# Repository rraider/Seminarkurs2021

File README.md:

# Seminarkurs2021

  Entwicklung eines turingvollständigen, primitiven Microcontroller in der Software Digital
  
  Sponsored by JLCPCB https://jlcpcb.com/RAT

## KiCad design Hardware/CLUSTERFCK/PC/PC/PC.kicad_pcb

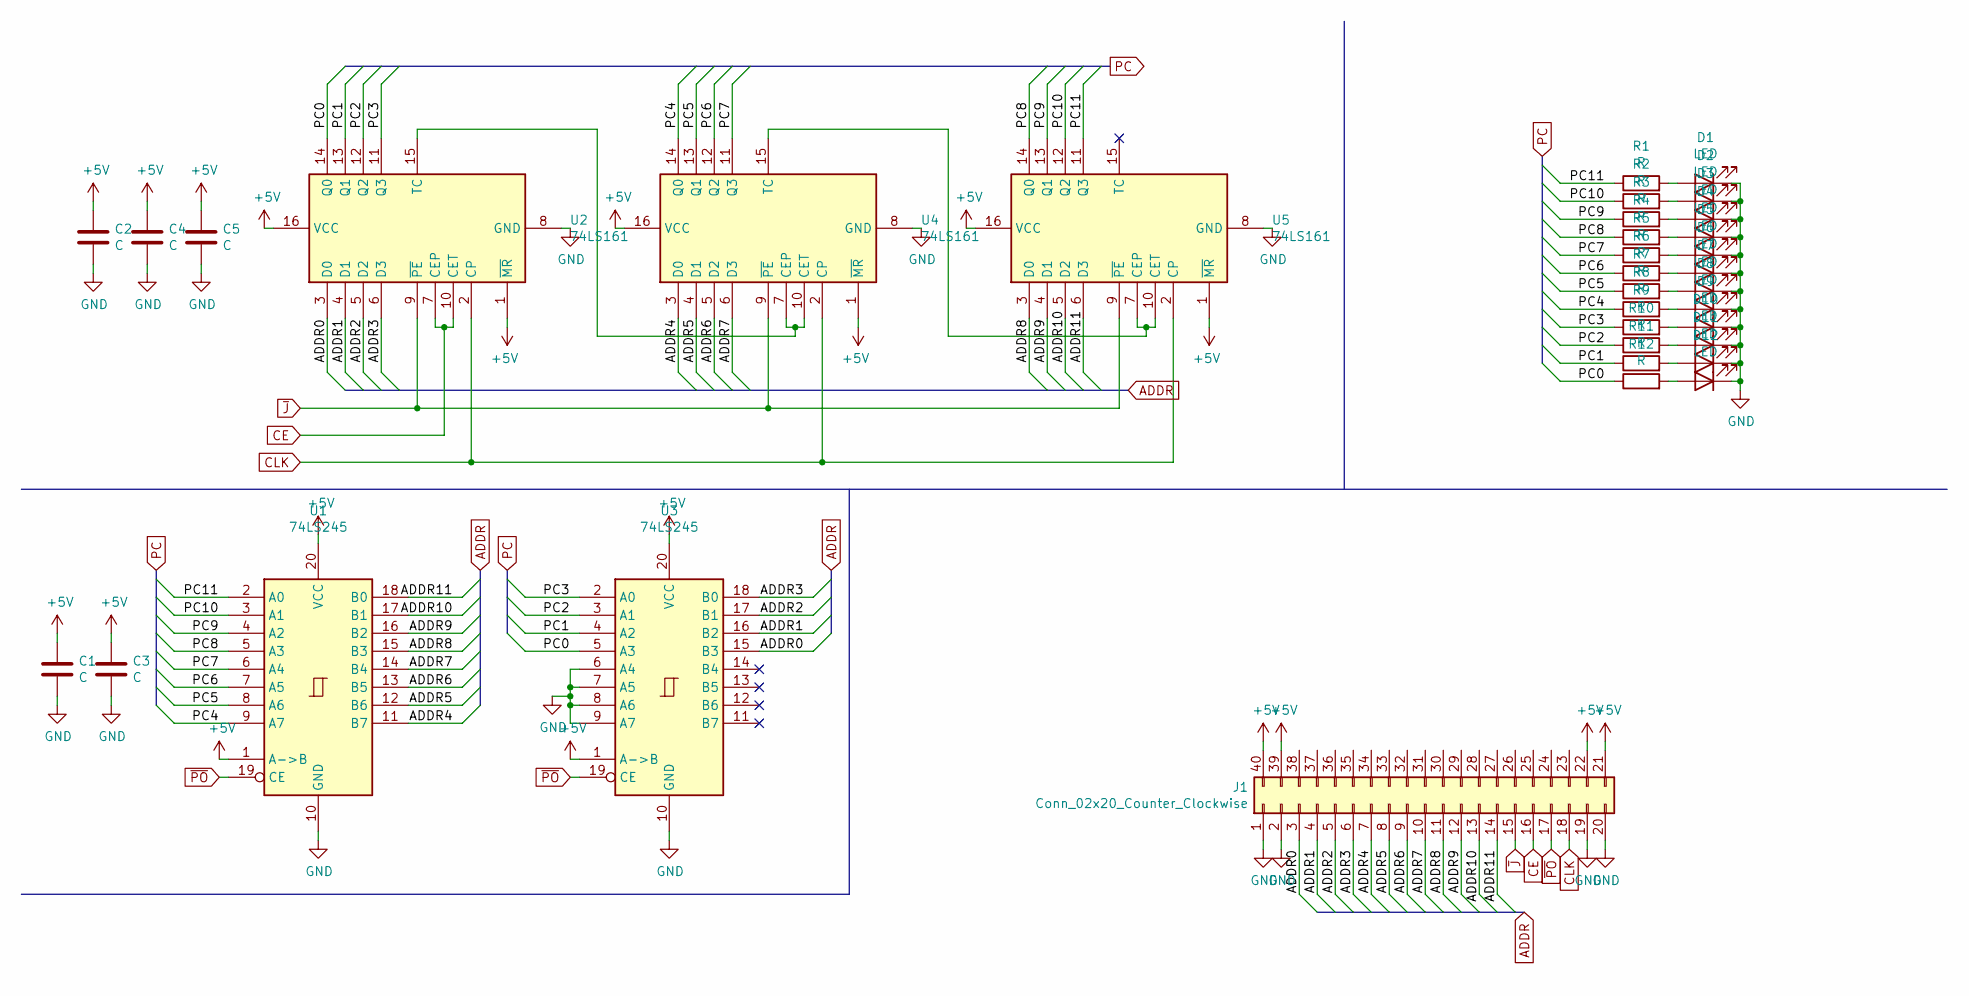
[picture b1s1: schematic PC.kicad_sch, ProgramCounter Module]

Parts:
C1, C2, C3, C4, C5: C; C_0805_2012Metric_Pad1.15x1.40mm_HandSolder
D1, D2, D3, D4, D5, D6, D7, D8, D9, D10, D11, D12: LED; LED_D5.0mm
J1: Conn_02x20_Counter_Clockwise; PinSocket_2x20_P2.54mm_Horizontal
R1, R2, R3, R4, R5, R6, R7, R8, R9, R10, R11, R12: R; R_0805_2012Metric_Pad1.15x1.40mm_HandSolder
U1, U3: 74LS245; SOIC-20W_7.5x12.8mm_P1.27mm
U2, U4, U5: 74LS161; SOIC-16_3.9x9.9mm_P1.27mm

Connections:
+5V: C1.1, C2.1, C3.1, C4.1, C5.1, J1.21, J1.22, J1.39, J1.40, U1.1 (A->B), U1.20 (VCC), U2.1 (~MR), U2.16 (VCC), U3.1 (A->B), U3.20 (VCC), U4.1 (~MR), U4.16 (VCC), U5.1 (~MR), U5.16 (VCC)
/ADDR0: J1.3, U2.3 (D0), U3.15 (B3)
/ADDR1: J1.4, U2.4 (D1), U3.16 (B2)
/ADDR2: J1.5, U2.5 (D2), U3.17 (B1)
/ADDR3: J1.6, U2.6 (D3), U3.18 (B0)
/ADDR4: J1.7, U1.11 (B7), U4.3 (D0)
/ADDR5: J1.8, U1.12 (B6), U4.4 (D1)
/ADDR6: J1.9, U1.13 (B5), U4.5 (D2)
/ADDR7: J1.10, U1.14 (B4), U4.6 (D3)
/ADDR8: J1.11, U1.15 (B3), U5.3 (D0)
/ADDR9: J1.12, U1.16 (B2), U5.4 (D1)
/ADDR10: J1.13, U1.17 (B1), U5.5 (D2)
/ADDR11: J1.14, U1.18 (B0), U5.6 (D3)
/PC0: R12.1, U2.14 (Q0), U3.5 (A3)
/PC1: R11.1, U2.13 (Q1), U3.4 (A2)
/PC2: R10.1, U2.12 (Q2), U3.3 (A1)
/PC3: R9.1, U2.11 (Q3), U3.2 (A0)
/PC4: R8.1, U1.9 (A7), U4.14 (Q0)
/PC5: R7.1, U1.8 (A6), U4.13 (Q1)
/PC6: R6.1, U1.7 (A5), U4.12 (Q2)
/PC7: R5.1, U1.6 (A4), U4.11 (Q3)
/PC8: R4.1, U1.5 (A3), U5.14 (Q0)
/PC9: R3.1, U1.4 (A2), U5.13 (Q1)
/PC10: R2.1, U1.3 (A1), U5.12 (Q2)
/PC11: R1.1, U1.2 (A0), U5.11 (Q3)
CE: J1.16, U2.7 (CEP), U2.10 (CET)
CLK: J1.18, U2.2 (CP), U4.2 (CP), U5.2 (CP)
GND: C1.2, C2.2, C3.2, C4.2, C5.2, D1.1 (K), D2.1 (K), D3.1 (K), D4.1 (K), D5.1 (K), D6.1 (K), D7.1 (K), D8.1 (K), D9.1 (K), D10.1 (K), D11.1 (K), D12.1 (K), J1.1, J1.2, J1.19, J1.20, U1.10 (GND), U2.8 (GND), U3.6 (A4), U3.7 (A5), U3.8 (A6), U3.9 (A7), U3.10 (GND), U4.8 (GND), U5.8 (GND)
unnamed: D1.2 (A), R1.2
unnamed: D2.2 (A), R2.2
unnamed: D3.2 (A), R3.2
unnamed: D4.2 (A), R4.2
unnamed: D5.2 (A), R5.2
unnamed: D6.2 (A), R6.2
unnamed: D7.2 (A), R7.2
unnamed: D8.2 (A), R8.2
unnamed: D9.2 (A), R9.2
unnamed: D10.2 (A), R10.2
unnamed: D11.2 (A), R11.2
unnamed: D12.2 (A), R12.2
unnamed: U2.15 (TC), U4.7 (CEP), U4.10 (CET)
unnamed: U4.15 (TC), U5.7 (CEP), U5.10 (CET)
~J: J1.15, U2.9 (~PE), U4.9 (~PE), U5.9 (~PE)
~PO: J1.17, U1.19 (CE), U3.19 (CE)

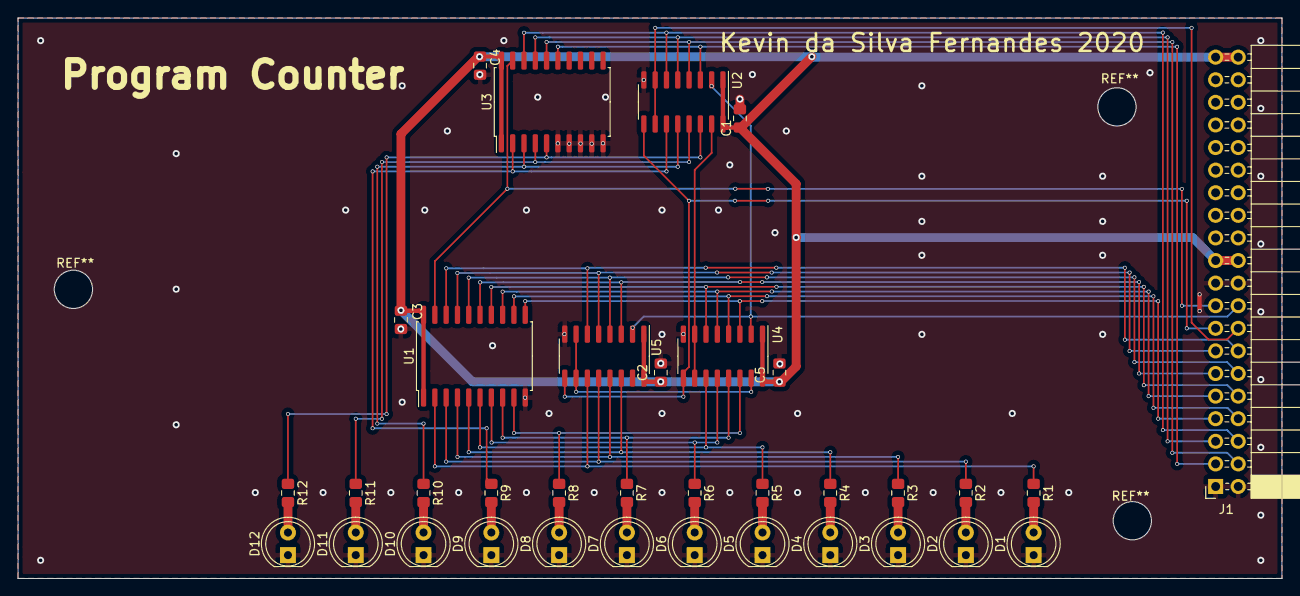
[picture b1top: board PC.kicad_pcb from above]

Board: 2 copper layers, 142.1 x 63.0 mm, 35 parts (0 on the bottom side), 44 nets.

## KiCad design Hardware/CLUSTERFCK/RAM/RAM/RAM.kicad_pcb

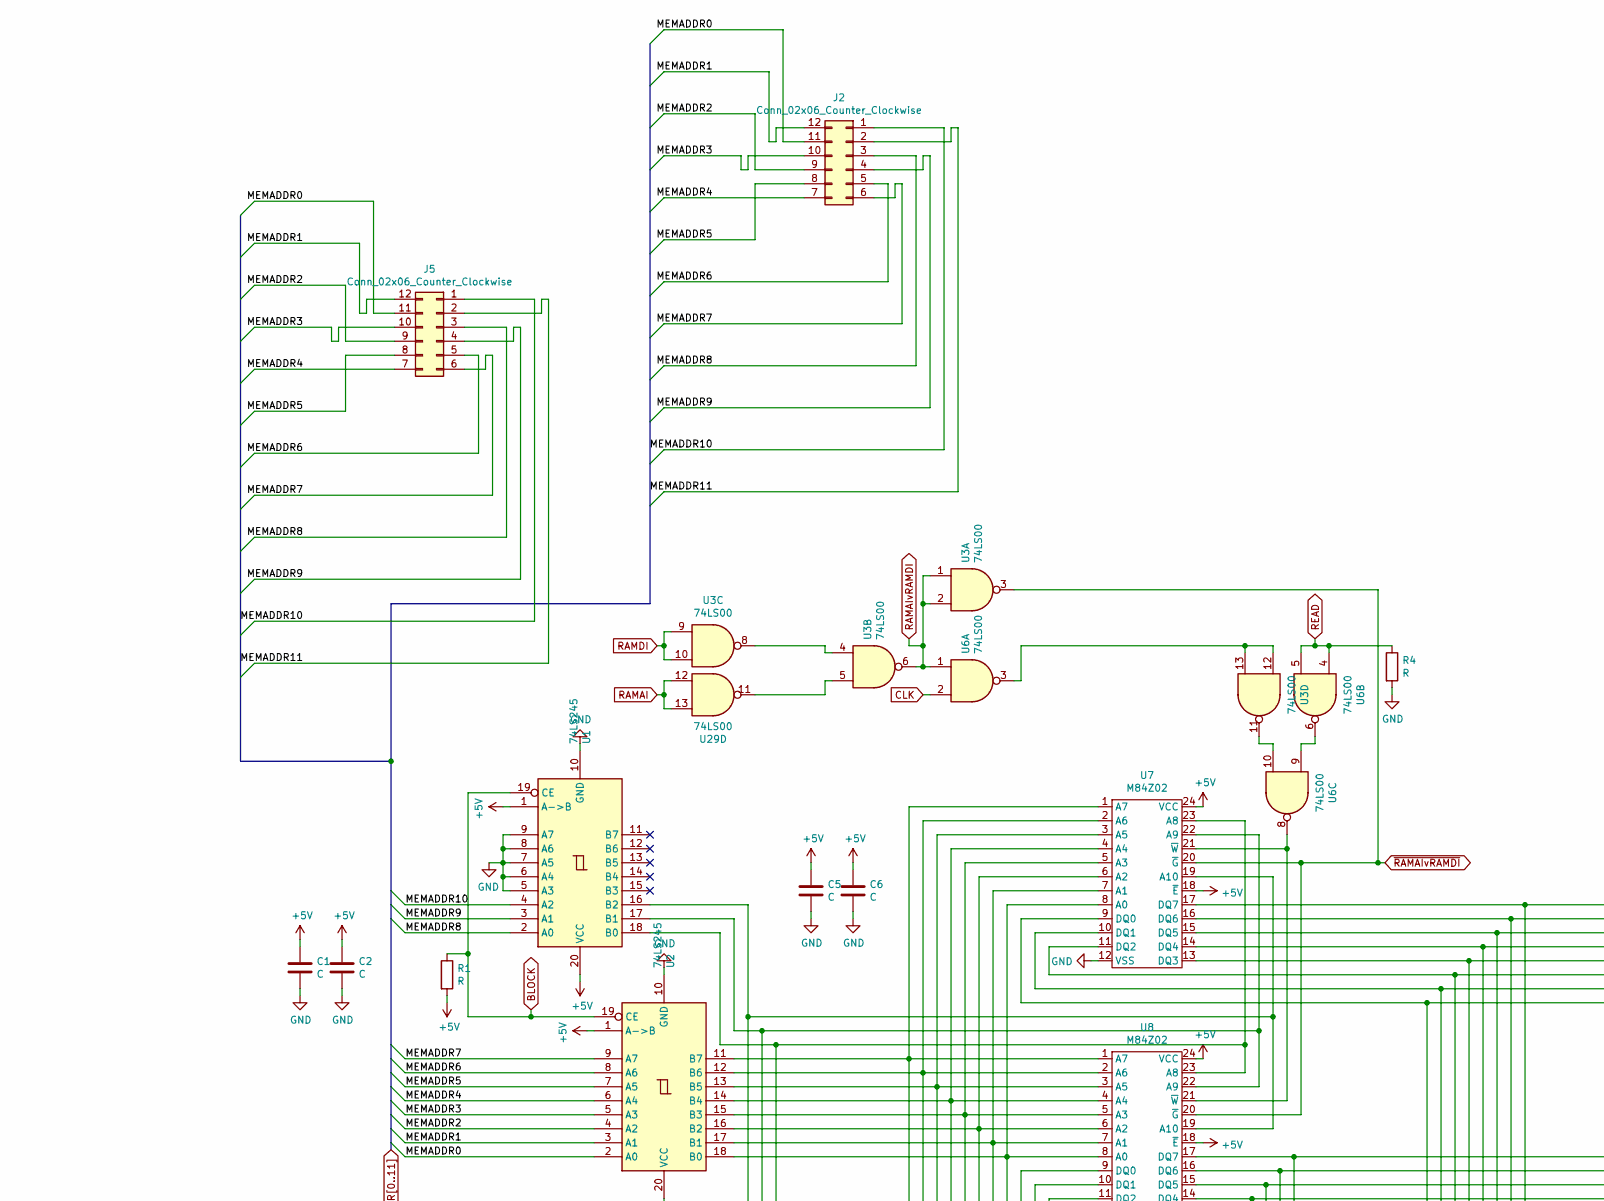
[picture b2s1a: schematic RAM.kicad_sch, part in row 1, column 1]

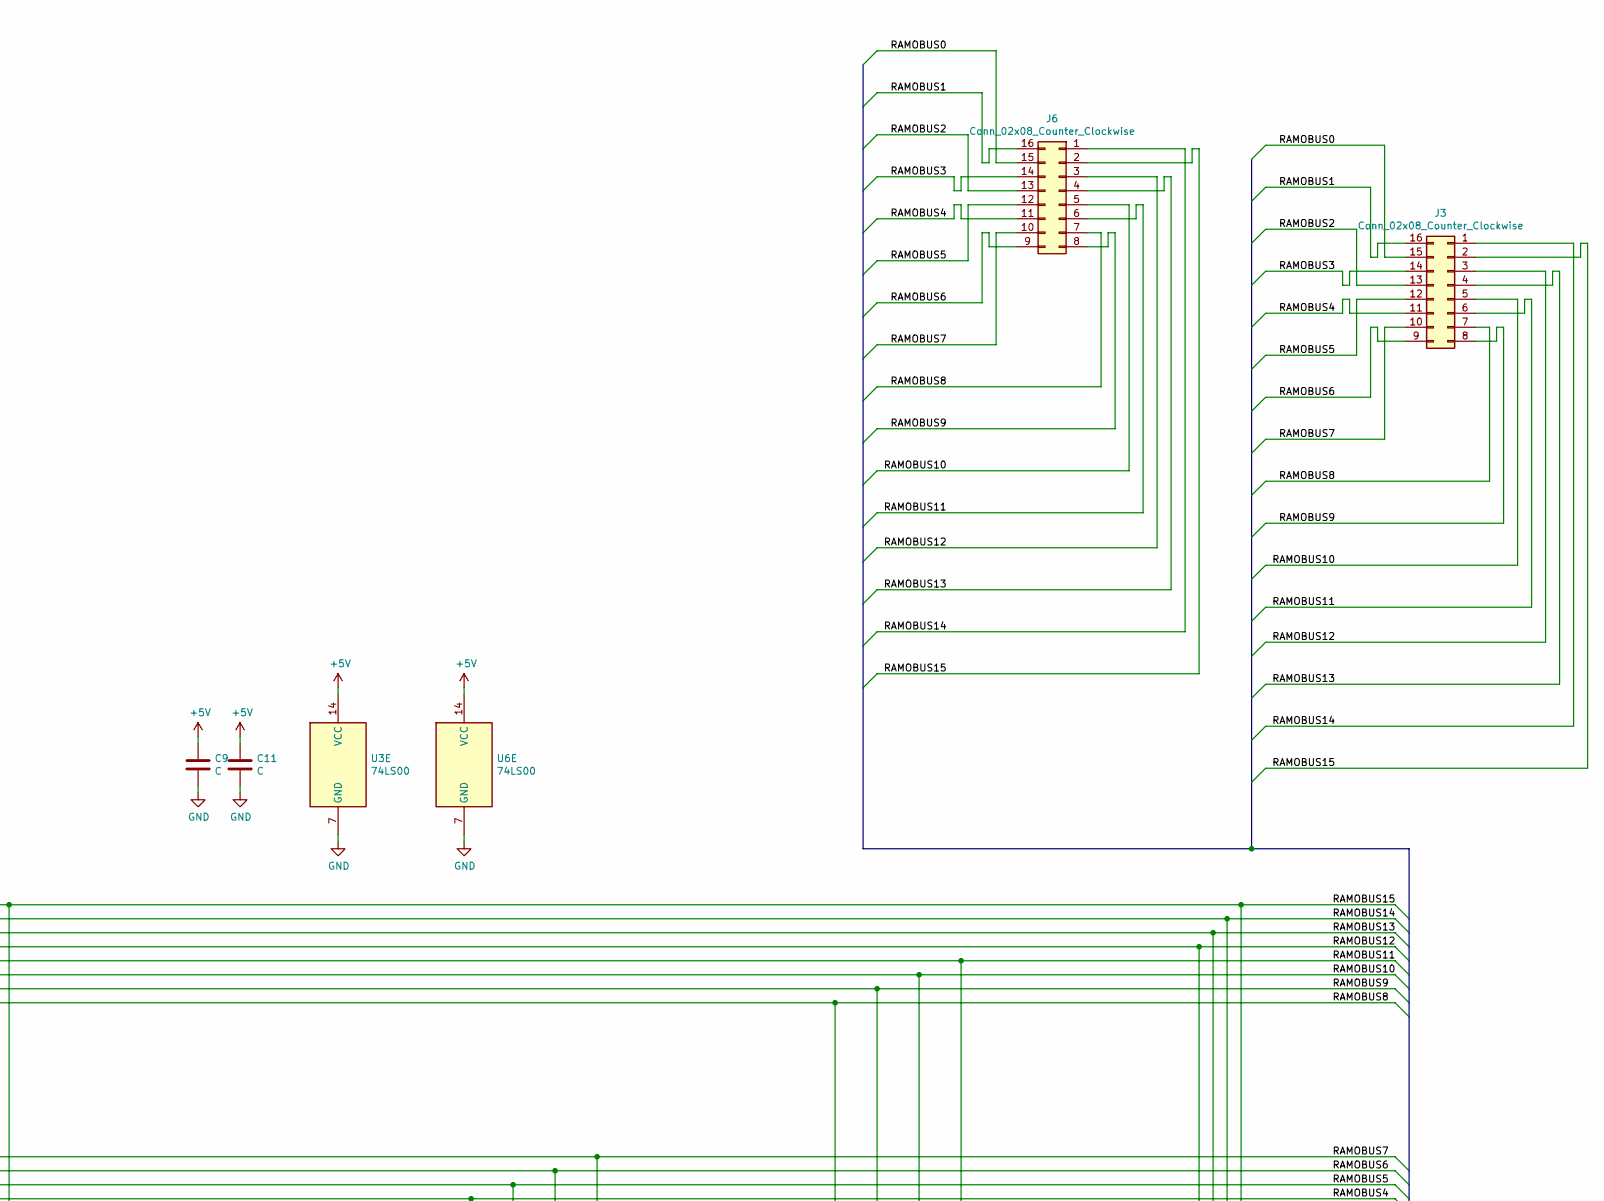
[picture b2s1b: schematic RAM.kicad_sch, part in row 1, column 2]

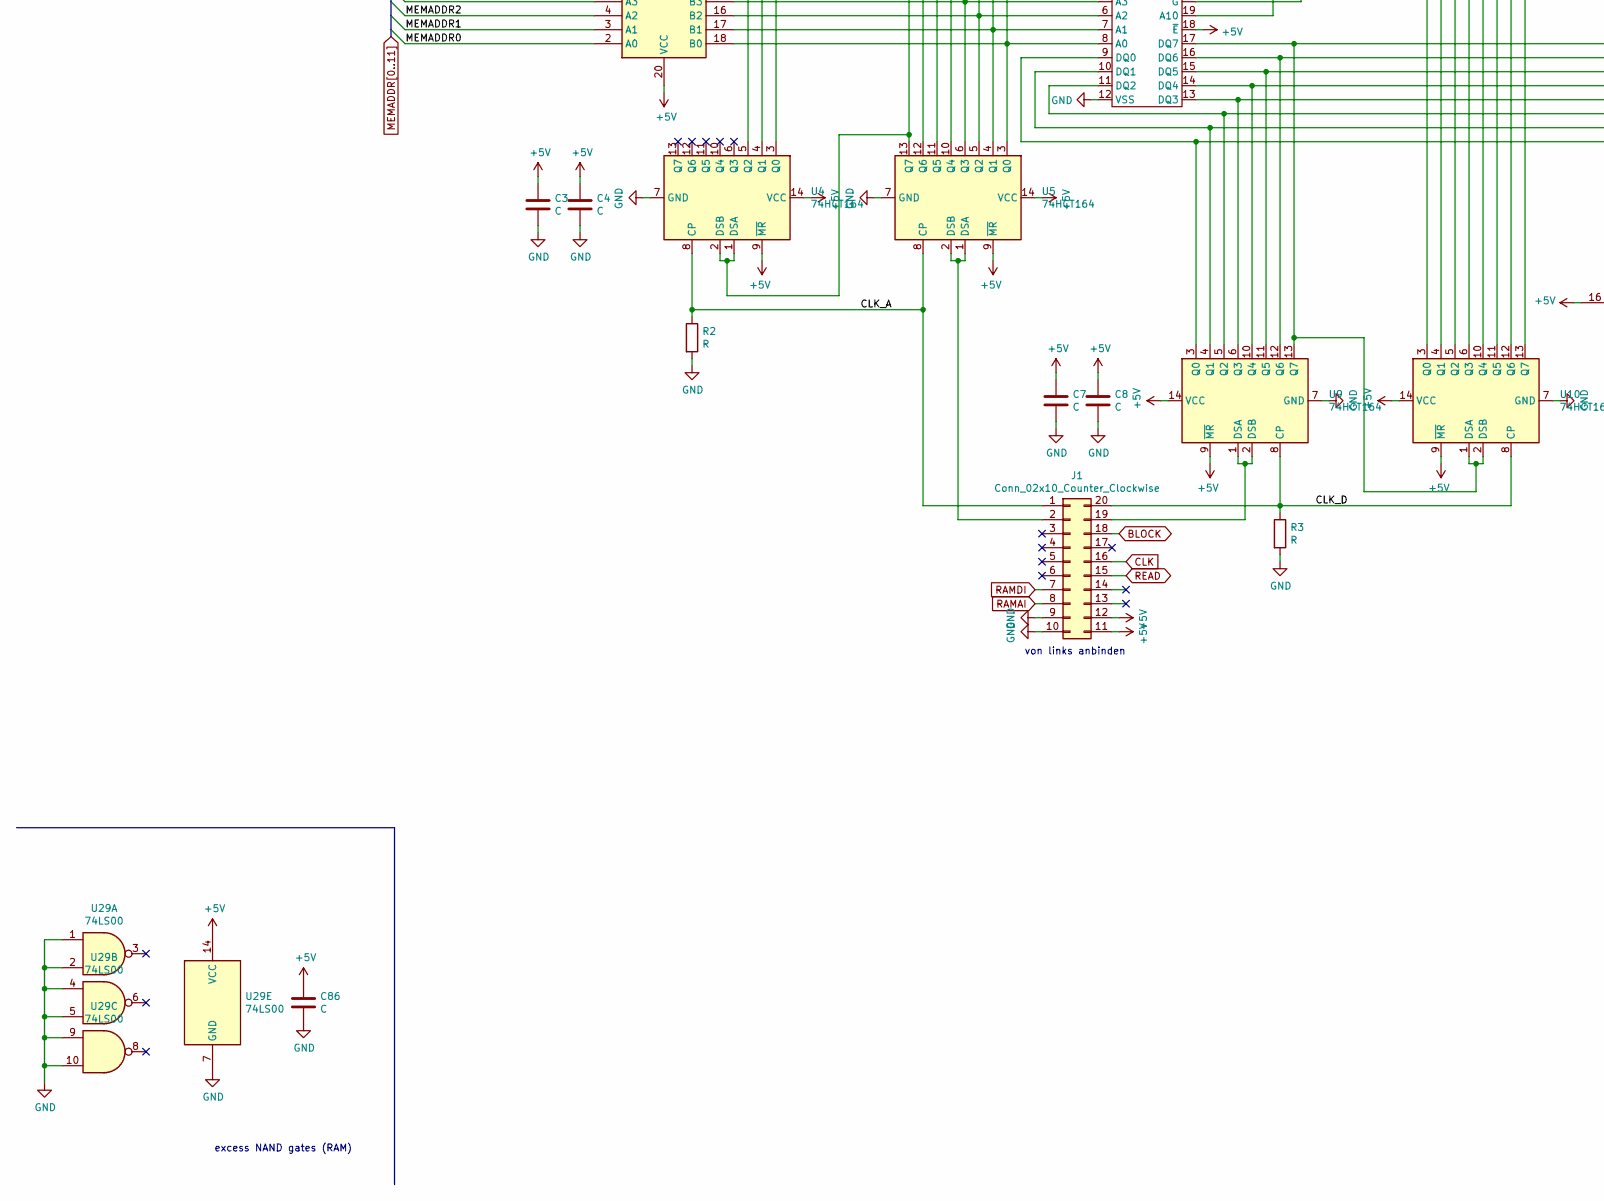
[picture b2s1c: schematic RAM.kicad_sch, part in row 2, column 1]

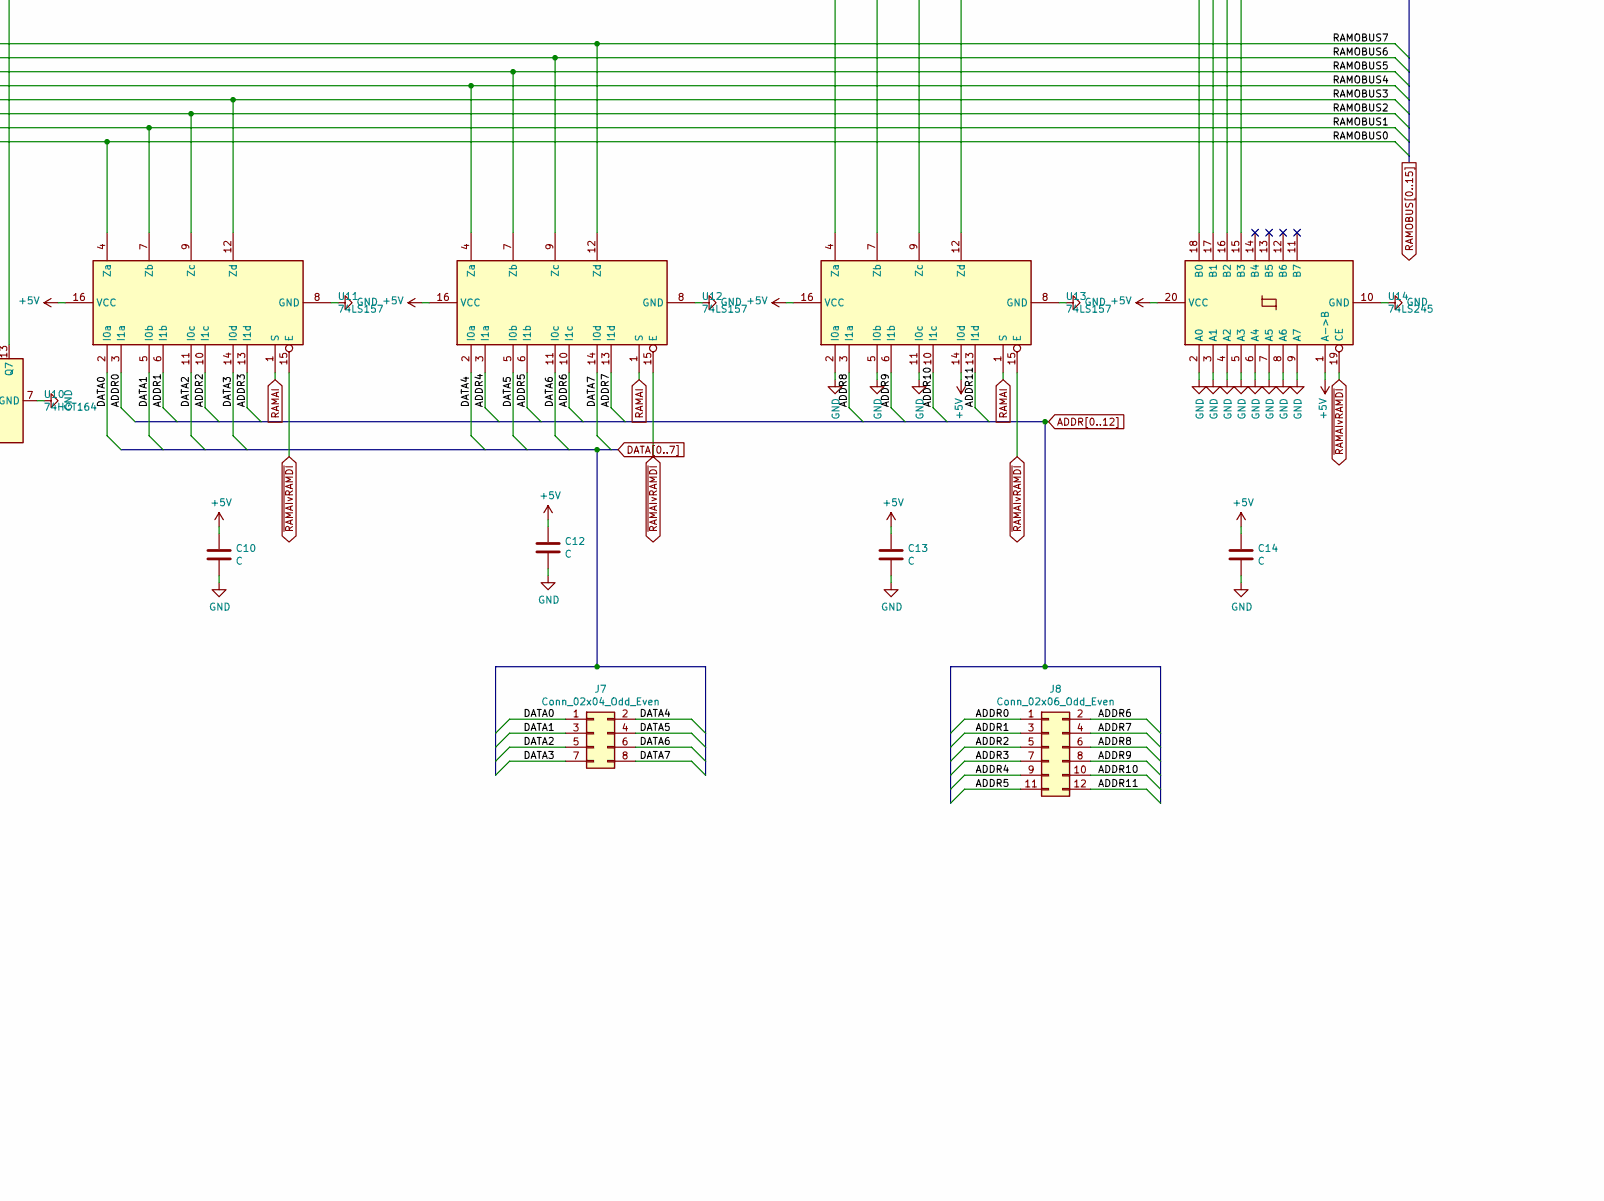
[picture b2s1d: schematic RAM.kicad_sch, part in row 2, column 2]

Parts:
C1, C2, C3, C4, C5, C6, C7, C8, C9, C10, C11, C12, C13, C14, C86: C; C_0805_2012Metric_Pad1.15x1.40mm_HandSolder
J1: Conn_02x10_Counter_Clockwise; PinHeader_2x10_P2.54mm_Horizontal
J2: Conn_02x06_Counter_Clockwise; PinHeader_2x06_P2.54mm_Vertical
J3: Conn_02x08_Counter_Clockwise; PinHeader_2x08_P2.54mm_Vertical
J5: Conn_02x06_Counter_Clockwise; PinHeader_2x06_P2.54mm_Horizontal
J6: Conn_02x08_Counter_Clockwise; PinHeader_2x08_P2.54mm_Horizontal
J7: Conn_02x04_Odd_Even; PinHeader_2x04_P2.54mm_Horizontal
J8: Conn_02x06_Odd_Even; PinHeader_2x06_P2.54mm_Horizontal
R1, R2, R3, R4: R; R_0805_2012Metric
U1, U2, U14: 74LS245; TSSOP-20_4.4x6.5mm_P0.65mm
U3, U6, U29: 74LS00; SOIC-14W_7.5x9mm_P1.27mm
U4, U5, U9, U10: 74HCT164; SOIC-14_3.9x8.7mm_P1.27mm
U7, U8: M84Z02; DIP-24_W15.24mm_Socket_LongPads
U11, U12, U13: 74LS157; SOIC-16_3.9x9.9mm_P1.27mm

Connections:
+5V: C1.1, C2.1, C3.1, C4.1, C5.1, C6.1, C7.1, C8.1, C9.1, C10.1, C11.1, C12.1, C13.1, C14.1, C86.1, J1.11, J1.12, R1.2, U1.1 (A->B), U1.20 (VCC), U2.1 (A->B), U2.20 (VCC), U3.14 (VCC), U4.9 (~MR), U4.14 (VCC), U5.9 (~MR), U5.14 (VCC), U6.14 (VCC), U7.18 (~E), U7.24 (VCC), U8.18 (~E), U8.24 (VCC), U9.9 (~MR), U9.14 (VCC), U10.9 (~MR), U10.14 (VCC), U11.16 (VCC), U12.16 (VCC), U13.14 (I0d), U13.16 (VCC), U14.1 (A->B), U14.20 (VCC), U29.14 (VCC)
/CLK_A: J1.1, R2.1, U4.8 (CP), U5.8 (CP)
/CLK_D: J1.20, R3.1, U9.8 (CP), U10.8 (CP)
ADDR0: J8.1, U11.3 (I1a)
ADDR1: J8.3, U11.6 (I1b)
ADDR2: J8.5, U11.10 (I1c)
ADDR3: J8.7, U11.13 (I1d)
ADDR4: J8.9, U12.3 (I1a)
ADDR5: J8.11, U12.6 (I1b)
ADDR6: J8.2, U12.10 (I1c)
ADDR7: J8.4, U12.13 (I1d)
ADDR8: J8.6, U13.3 (I1a)
ADDR9: J8.8, U13.6 (I1b)
ADDR10: J8.10, U13.10 (I1c)
ADDR11: J8.12, U13.13 (I1d)
BLOCK: J1.18, R1.1, U1.19 (CE), U2.19 (CE)
CLK: J1.16, U6.2
DATA0: J7.1, U11.2 (I0a)
DATA1: J7.3, U11.5 (I0b)
DATA2: J7.5, U11.11 (I0c)
DATA3: J7.7, U11.14 (I0d)
DATA4: J7.2, U12.2 (I0a)
DATA5: J7.4, U12.5 (I0b)
DATA6: J7.6, U12.11 (I0c)
DATA7: J7.8, U12.14 (I0d)
GND: C1.2, C2.2, C3.2, C4.2, C5.2, C6.2, C7.2, C8.2, C9.2, C10.2, C11.2, C12.2, C13.2, C14.2, C86.2, J1.9, J1.10, R2.2, R3.2, R4.2, U1.5 (A3), U1.6 (A4), U1.7 (A5), U1.8 (A6), U1.9 (A7), U1.10 (GND), U2.10 (GND), U3.7 (GND), U4.7 (GND), U5.7 (GND), U6.7 (GND), U7.12 (VSS), U8.12 (VSS), U9.7 (GND), U10.7 (GND), U11.8 (GND), U12.8 (GND), U13.2 (I0a), U13.5 (I0b), U13.8 (GND), U13.11 (I0c), U14.2 (A0), U14.3 (A1), U14.4 (A2), U14.5 (A3), U14.6 (A4), U14.7 (A5), U14.8 (A6), U14.9 (A7), U14.10 (GND), U29.1, U29.2, U29.4, U29.5, U29.7 (GND), U29.9, U29.10
MEMADDR0: J2.11, J5.11, U2.2 (A0)
MEMADDR1: J2.12, J5.12, U2.3 (A1)
MEMADDR2: J2.9, J5.9, U2.4 (A2)
MEMADDR3: J2.10, J5.10, U2.5 (A3)
MEMADDR4: J2.7, J5.7, U2.6 (A4)
MEMADDR5: J2.8, J5.8, U2.7 (A5)
MEMADDR6: J2.5, J5.5, U2.8 (A6)
MEMADDR7: J2.6, J5.6, U2.9 (A7)
MEMADDR8: J2.3, J5.3, U1.2 (A0)
MEMADDR9: J2.4, J5.4, U1.3 (A1)
MEMADDR10: J2.1, J5.1, U1.4 (A2)
MEMADDR11: J2.2, J5.2
unnamed: J1.2, U5.1 (DSA), U5.2 (DSB)
unnamed: J1.19, U9.1 (DSA), U9.2 (DSB)
unnamed: U1.16 (B2), U4.5 (Q2), U7.19 (A10), U8.19 (A10)
unnamed: U1.17 (B1), U4.4 (Q1), U7.22 (A9), U8.22 (A9)
unnamed: U1.18 (B0), U4.3 (Q0), U7.23 (A8), U8.23 (A8)
unnamed: U2.11 (B7), U4.1 (DSA), U4.2 (DSB), U5.13 (Q7), U7.1 (A7), U8.1 (A7)
unnamed: U2.12 (B6), U5.12 (Q6), U7.2 (A6), U8.2 (A6)
unnamed: U2.13 (B5), U5.11 (Q5), U7.3 (A5), U8.3 (A5)
unnamed: U2.14 (B4), U5.10 (Q4), U7.4 (A4), U8.4 (A4)
unnamed: U2.15 (B3), U5.6 (Q3), U7.5 (A3), U8.5 (A3)
unnamed: U2.16 (B2), U5.5 (Q2), U7.6 (A2), U8.6 (A2)
unnamed: U2.17 (B1), U5.4 (Q1), U7.7 (A1), U8.7 (A1)
unnamed: U2.18 (B0), U5.3 (Q0), U7.8 (A0), U8.8 (A0)
unnamed: U3.4, U3.8
unnamed: U3.11, U6.10
unnamed: U3.12, U3.13, U6.3
unnamed: U6.6, U6.9
unnamed: U6.8, U7.21 (~W), U8.21 (~W)
unnamed: U3.5, U29.11
RAMAI: J1.8, U11.1 (S), U12.1 (S), U13.1 (S), U29.12, U29.13
RAMAIvRAMDI: U3.1, U3.2, U3.6, U6.1
RAMDI: J1.7, U3.9, U3.10
RAMOBUS0: J3.15, J6.15, U8.9 (DQ0), U9.3 (Q0), U11.4 (Za)
RAMOBUS1: J3.16, J6.16, U8.10 (DQ1), U9.4 (Q1), U11.7 (Zb)
RAMOBUS2: J3.13, J6.13, U8.11 (DQ2), U9.5 (Q2), U11.9 (Zc)
RAMOBUS3: J3.14, J6.14, U8.13 (DQ3), U9.6 (Q3), U11.12 (Zd)
RAMOBUS4: J3.11, J6.11, U8.14 (DQ4), U9.10 (Q4), U12.4 (Za)
RAMOBUS5: J3.12, J6.12, U8.15 (DQ5), U9.11 (Q5), U12.7 (Zb)
RAMOBUS6: J3.9, J6.9, U8.16 (DQ6), U9.12 (Q6), U12.9 (Zc)
RAMOBUS7: J3.10, J6.10, U8.17 (DQ7), U9.13 (Q7), U10.1 (DSA), U10.2 (DSB), U12.12 (Zd)
RAMOBUS8: J3.7, J6.7, U7.9 (DQ0), U10.3 (Q0), U13.4 (Za)
RAMOBUS9: J3.8, J6.8, U7.10 (DQ1), U10.4 (Q1), U13.7 (Zb)
RAMOBUS10: J3.5, J6.5, U7.11 (DQ2), U10.5 (Q2), U13.9 (Zc)
RAMOBUS11: J3.6, J6.6, U7.13 (DQ3), U10.6 (Q3), U13.12 (Zd)
RAMOBUS12: J3.3, J6.3, U7.14 (DQ4), U10.10 (Q4), U14.18 (B0)
RAMOBUS13: J3.4, J6.4, U7.15 (DQ5), U10.11 (Q5), U14.17 (B1)
RAMOBUS14: J3.1, J6.1, U7.16 (DQ6), U10.12 (Q6), U14.16 (B2)
RAMOBUS15: J3.2, J6.2, U7.17 (DQ7), U10.13 (Q7), U14.15 (B3)
READ: J1.15, R4.1, U6.4, U6.5
~RAMAIvRAMDI: U3.3, U7.20 (~G), U8.20 (~G), U11.15 (E), U12.15 (E), U13.15 (E), U14.19 (CE)

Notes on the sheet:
excess NAND gates (RAM)
von links anbinden

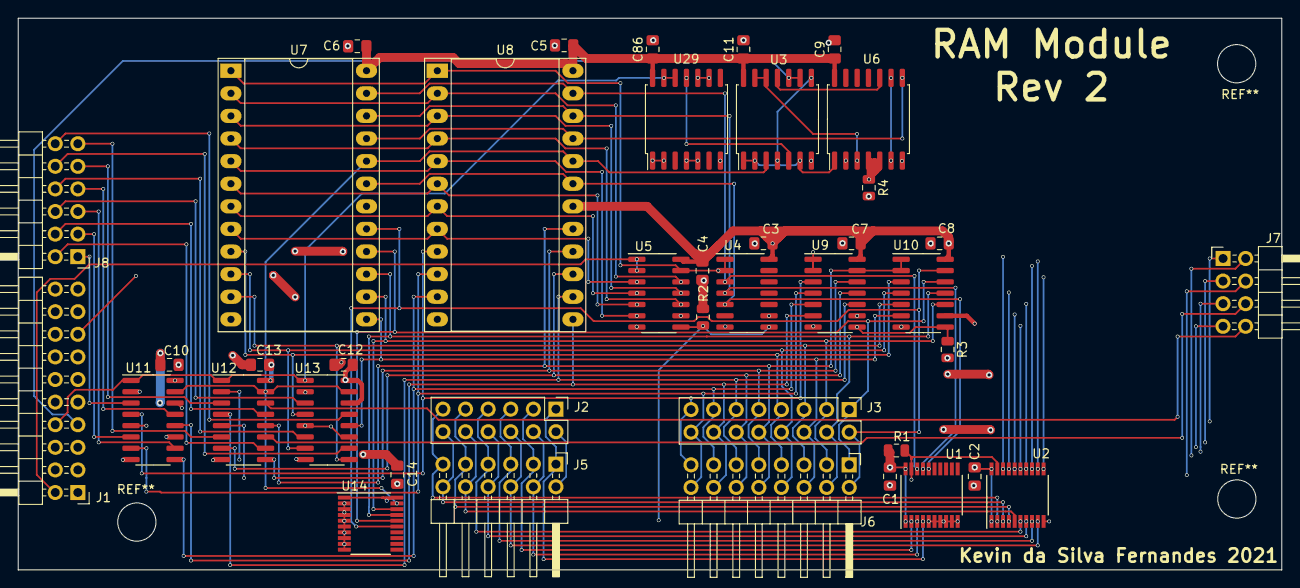
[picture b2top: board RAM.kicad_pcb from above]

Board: 4 copper layers, 142.0 x 62.0 mm, 41 parts (0 on the bottom side), 78 nets.

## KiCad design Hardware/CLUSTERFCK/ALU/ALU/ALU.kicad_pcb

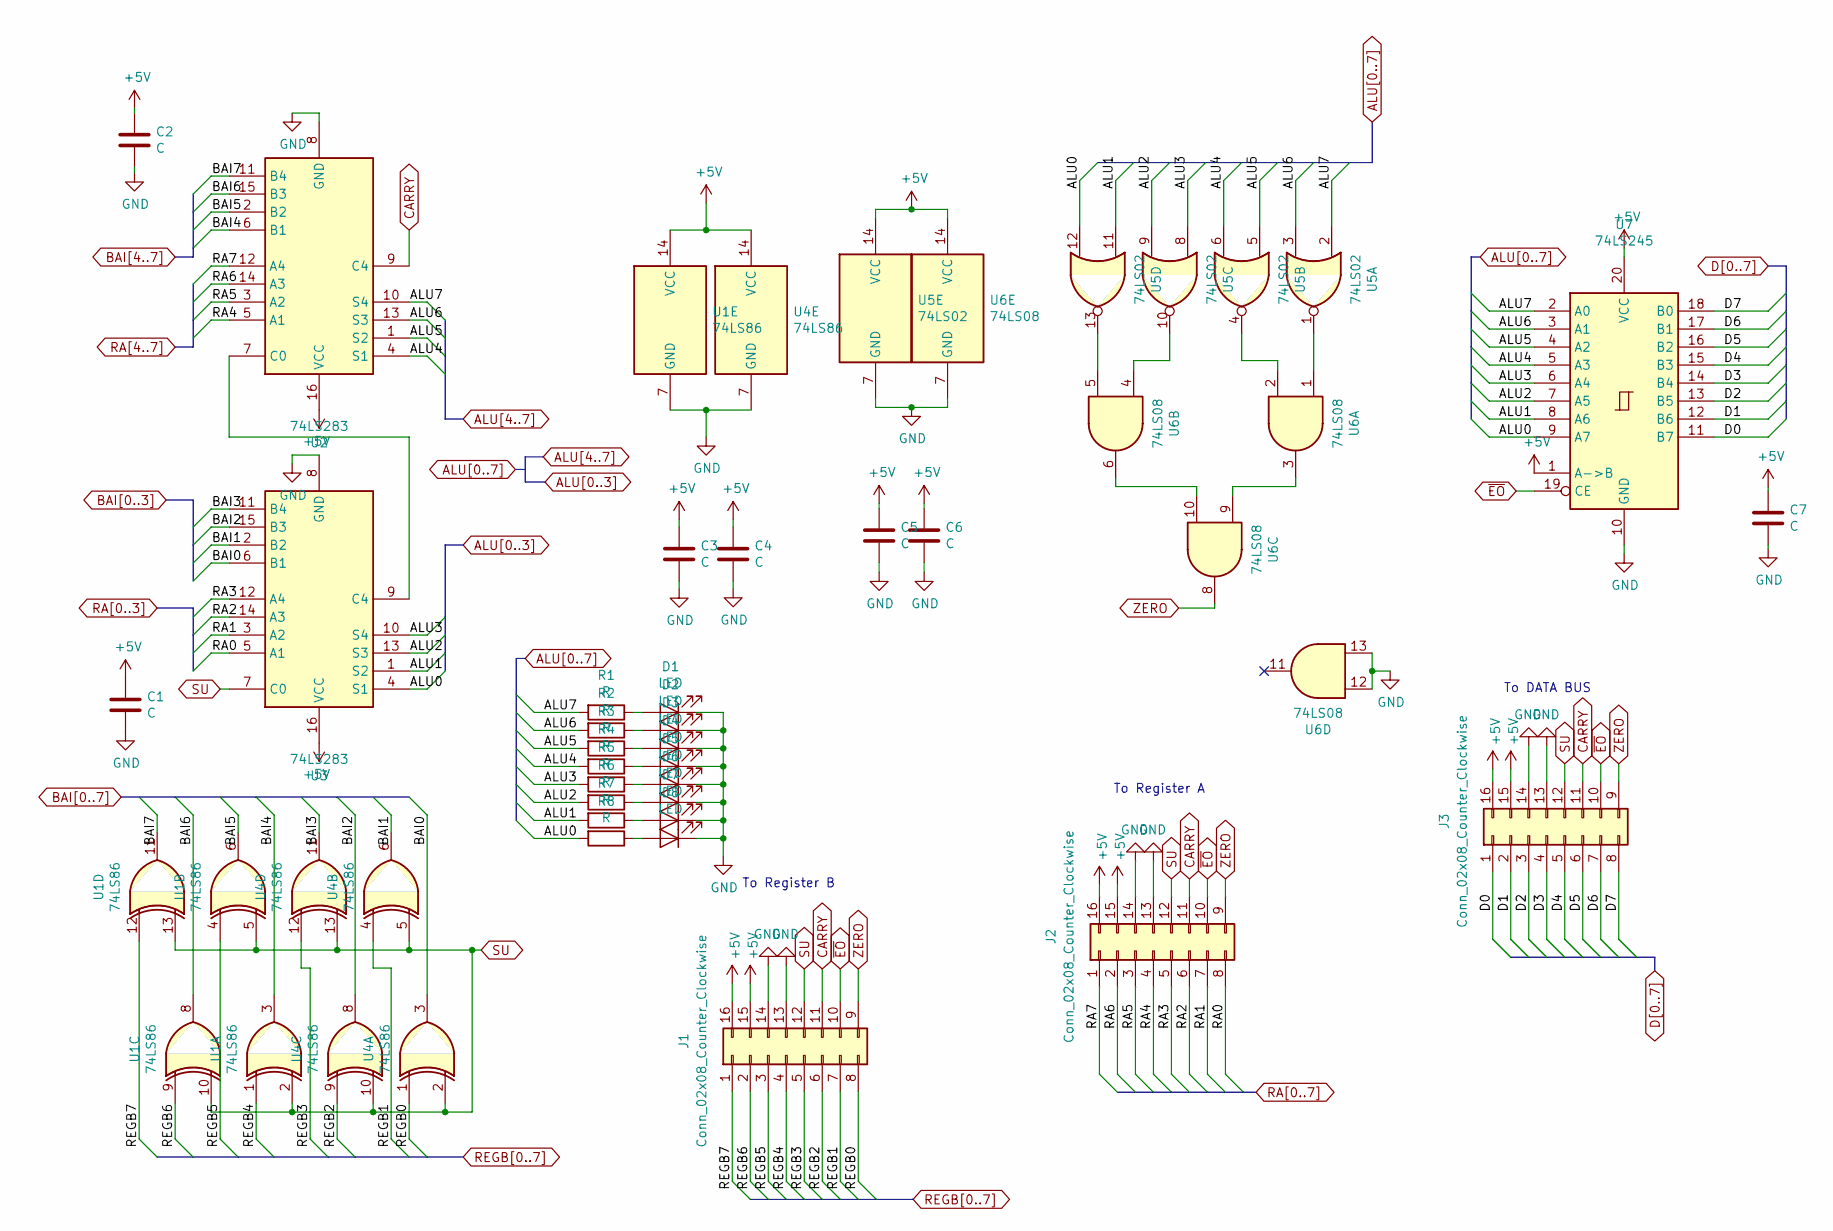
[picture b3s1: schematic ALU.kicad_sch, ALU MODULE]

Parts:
C1, C2, C3, C4, C5, C6, C7: C; C_0805_2012Metric_Pad1.15x1.40mm_HandSolder
D1, D2, D3, D4, D5, D6, D7, D8: LED; LED_D5.0mm
J1, J2, J3: Conn_02x08_Counter_Clockwise
R1, R2, R3, R4, R5, R6, R7, R8: R; R_0805_2012Metric_Pad1.15x1.40mm_HandSolder
U1, U4: 74LS86; DIP-14_W7.62mm_Socket_LongPads
U2, U3: 74LS283; SOIC-16W_5.3x10.2mm_P1.27mm
U5: 74LS02; SOIC-14_3.9x8.7mm_P1.27mm
U6: 74LS08; SOIC-14_3.9x8.7mm_P1.27mm
U7: 74LS245; SOIC-20W_7.5x12.8mm_P1.27mm

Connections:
+5V: C1.1, C2.1, C3.1, C4.1, C5.1, C6.1, C7.1, J1.15, J1.16, J2.15, J2.16, J3.15, J3.16, U1.14 (VCC), U2.16 (VCC), U3.16 (VCC), U4.14 (VCC), U5.14 (VCC), U6.14 (VCC), U7.1 (A->B), U7.20 (VCC); also elsewhere on the board
ALU0: R8.2, U3.4 (S1), U5.12, U7.9 (A7); also elsewhere on the board
ALU1: R7.2, U3.1 (S2), U5.11, U7.8 (A6); also elsewhere on the board
ALU2: R6.2, U3.13 (S3), U5.9, U7.7 (A5); also elsewhere on the board
ALU3: R5.2, U3.10 (S4), U5.8, U7.6 (A4); also elsewhere on the board
ALU4: R4.2, U2.4 (S1), U5.6, U7.5 (A3); also elsewhere on the board
ALU5: R3.2, U2.1 (S2), U5.5, U7.4 (A2); also elsewhere on the board
ALU6: R2.2, U2.13 (S3), U5.3, U7.3 (A1); also elsewhere on the board
ALU7: R1.2, U2.10 (S4), U5.2, U7.2 (A0); also elsewhere on the board
BAI0: U3.6 (B1), U4.3
BAI1: U3.2 (B2), U4.6
BAI2: U3.15 (B3), U4.8
BAI3: U3.11 (B4), U4.11
BAI4: U1.3, U2.6 (B1)
BAI5: U1.6, U2.2 (B2)
BAI6: U1.8, U2.15 (B3)
BAI7: U1.11, U2.11 (B4)
CARRY: J1.11, J2.11, J3.11, U2.9 (C4)
D0: J3.1, U7.11 (B7); also elsewhere on the board
D1: J3.2, U7.12 (B6); also elsewhere on the board
D2: J3.3, U7.13 (B5); also elsewhere on the board
D3: J3.4, U7.14 (B4); also elsewhere on the board
D4: J3.5, U7.15 (B3); also elsewhere on the board
D5: J3.6, U7.16 (B2); also elsewhere on the board
D6: J3.7, U7.17 (B1); also elsewhere on the board
D7: J3.8, U7.18 (B0); also elsewhere on the board
GND: C1.2, C2.2, C3.2, C4.2, C5.2, C6.2, C7.2, D1.1 (K), D2.1 (K), D3.1 (K), D4.1 (K), D5.1 (K), D6.1 (K), D7.1 (K), D8.1 (K), J1.13, J1.14, J2.13, J2.14, J3.13, J3.14, U1.7 (GND), U2.8 (GND), U3.8 (GND), U4.7 (GND), U5.7 (GND), U6.7 (GND), U6.12, U6.13, U7.10 (GND); also elsewhere on the board
unnamed: D1.2 (A), R1.1
unnamed: D2.2 (A), R2.1
unnamed: D3.2 (A), R3.1
unnamed: D4.2 (A), R4.1
unnamed: D5.2 (A), R5.1
unnamed: D6.2 (A), R6.1
unnamed: D7.2 (A), R7.1
unnamed: D8.2 (A), R8.1
unnamed: U2.7 (C0), U3.9 (C4)
unnamed: U5.1, U6.1
unnamed: U5.4, U6.2
unnamed: U5.10, U6.4
unnamed: U5.13, U6.5
unnamed: U6.3, U6.9
unnamed: U6.6, U6.10
RA0: J2.8, U3.5 (A1)
RA1: J2.7, U3.3 (A2)
RA2: J2.6, U3.14 (A3)
RA3: J2.5, U3.12 (A4)
RA4: J2.4, U2.5 (A1)
RA5: J2.3, U2.3 (A2)
RA6: J2.2, U2.14 (A3)
RA7: J2.1, U2.12 (A4)
REGB0: J1.8, U4.1
REGB1: J1.7, U4.4
REGB2: J1.6, U4.9
REGB3: J1.5, U4.12
REGB4: J1.4, U1.1
REGB5: J1.3, U1.4
REGB6: J1.2, U1.9
REGB7: J1.1, U1.12
SU: J1.12, J2.12, J3.12, U1.2, U1.5, U1.10, U1.13, U3.7 (C0), U4.2, U4.5, U4.10, U4.13
ZERO: J1.9, J2.9, J3.9, U6.8
~EO: J1.10, J2.10, J3.10, U7.19 (CE); also elsewhere on the board

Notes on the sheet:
To Register B
To Register A
To DATA BUS

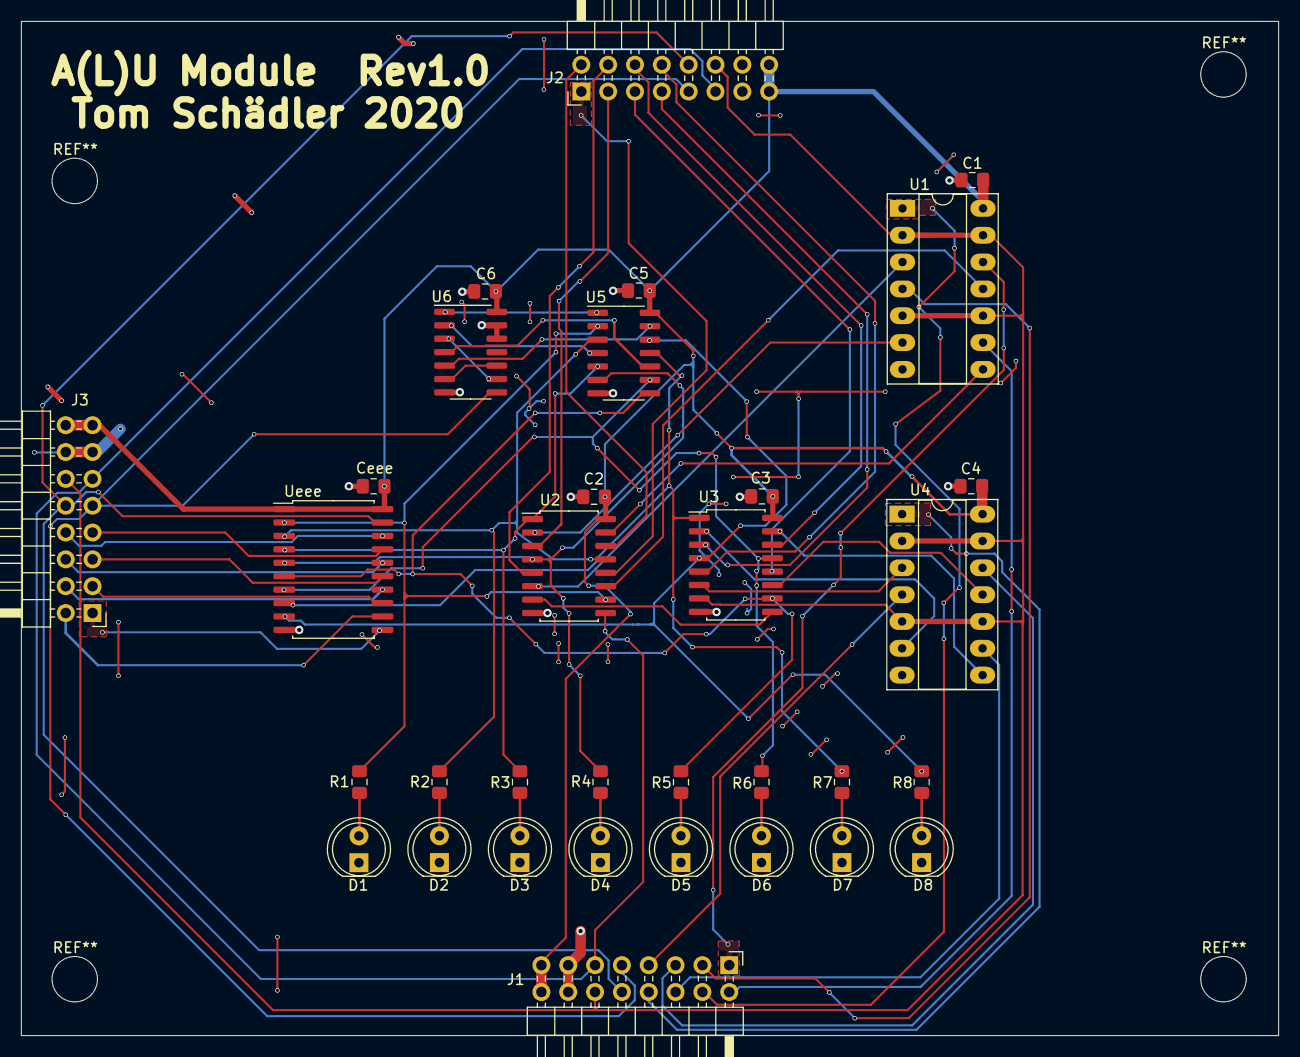
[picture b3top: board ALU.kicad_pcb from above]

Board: 2 copper layers, 119.0 x 96.0 mm, 33 parts (0 on the bottom side), 61 nets.

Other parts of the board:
Ceee: C; C_0805_2012Metric_Pad1.15x1.40mm_HandSolder
Ueee: 74LS245; SOIC-20W_7.5x12.8mm_P1.27mm

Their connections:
+5V: Ceee.1, Ueee.1 (A->B), Ueee.20 (VCC); also elsewhere on the board
ALU0: Ueee.9 (A7); also elsewhere on the board
ALU1: Ueee.8 (A6); also elsewhere on the board
ALU2: Ueee.7 (A5); also elsewhere on the board
ALU3: Ueee.6 (A4); also elsewhere on the board
ALU4: Ueee.5 (A3); also elsewhere on the board
ALU5: Ueee.4 (A2); also elsewhere on the board
ALU6: Ueee.3 (A1); also elsewhere on the board
ALU7: Ueee.2 (A0); also elsewhere on the board
D0: Ueee.11 (B7); also elsewhere on the board
D1: Ueee.12 (B6); also elsewhere on the board
D2: Ueee.13 (B5); also elsewhere on the board
D3: Ueee.14 (B4); also elsewhere on the board
D4: Ueee.15 (B3); also elsewhere on the board
D5: Ueee.16 (B2); also elsewhere on the board
D6: Ueee.17 (B1); also elsewhere on the board
D7: Ueee.18 (B0); also elsewhere on the board
GND: Ceee.2, Ueee.10 (GND); also elsewhere on the board
~EO: Ueee.19 (CE); also elsewhere on the board
